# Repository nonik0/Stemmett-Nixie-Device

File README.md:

# Stemmett Nixie Device

## Description
A Nixie device that uses front-viewed [PL31 socket](https://tubes-store.com/product_info.php?products_id=101) Nixie tubes ([IN-4](https://www.tube-tester.com/sites/nixie/data/in-4/in-4-sh2.htm), [IN-7](https://www.tube-tester.com/sites/nixie/data/IN-7/in-7.htm), [IN-7A](https://www.swissnixie.com/tubes/IN7A/), IN-7B) in different orientations to create makeshift letters and spell things like names! The main board itself has 6 sockets for custom PL31 breakout boards, which have the nixie tube sockets in different orientations to rotate the Nixie tubes. By rotating the tubes we can pseudo-spell things, see images below for example (i.e. "7" rotated 180° to be an "L", or "m" rotated -90° to be a small-sized "E").

The hardware is designed in KiCad and all design files are included in the hardware directory. The hardware consists of the design of the main board PCB and three different versions of the PL31 socket breakout boards. The overall component choices target using simple through-hole components so the PCB is easier to debug, as it is my first PCB design. All cathodes of the nixie tubes are controlled with a single pin with serial, using three 74HC595 shift registers to control the input of the six old school К155ИД1 (K155ID1, SN74141) driver chips for each nixie tube. Each tube anode has a simple MOSFET circuit to be able to PWM each tube individually, allowing each tube to be individually dimmed or turned off. I am using the tiny awesome [NCH8200HV](https://www.tindie.com/products/omnixie/nch8200hv-nixie-high-voltage-power-module/) for the high voltage supply.

The firmware is a PlatformIO-based project targetting the [TinyS3](https://esp32s3.com/tinys3.html) ESP32 dev board. All source files are included in the firmware directory. The firmware will cycle through various different animations, returning to the configured name/word between each. It has a basic HTTP UX with REST interface to update settings--enable/disable animations, changing brightness, etc. It is simple to customize the firmware to any tube configuration by creating a new one in [board.h](firmware/board.h).

## Bowen Nixie Device
See the [Bowen Nixie Device README](hardware/kicad/bowen-nixie-device/README.md).

## Images

#### PCB Layout and Bare PCBs

#### Wood Block to Enclosure

#### Fitting and Finishing

#### Finished Enclosure

#### Alternate Enclosure

## Animations

<a href="images/glitch_anim.mp4">Glitch Animation</a>
<a href="images/random_scan_anim.mp4">Random Scan Animation</a>

TODO: animations in better lighting...

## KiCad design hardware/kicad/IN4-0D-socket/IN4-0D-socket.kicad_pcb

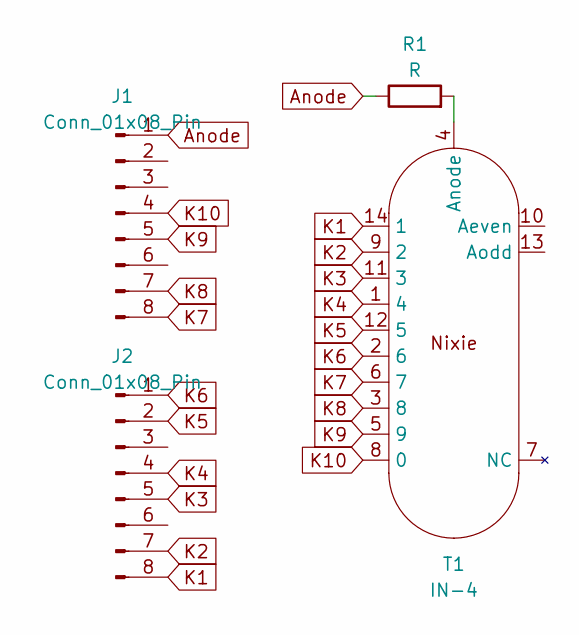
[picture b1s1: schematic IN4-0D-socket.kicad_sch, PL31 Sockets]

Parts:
J1, J2: Conn_01x08_Pin; PinHeader_1x08_P2.54mm_Vertical
R1: R; R_Axial_DIN0207_L6.3mm_D2.5mm_P7.62mm_Horizontal
T1: IN-4; PL31 (IN4 rotation)

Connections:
Anode: J1.1, R1.1
K1: J2.8, T1.14 (1)
K2: J2.7, T1.9 (2)
K3: J2.5, T1.11 (3)
K4: J2.4, T1.1 (4)
K5: J2.2, T1.12 (5)
K6: J2.1, T1.2 (6)
K7: J1.8, T1.6 (7)
K8: J1.7, T1.3 (8)
K9: J1.5, T1.5 (9)
K10: J1.4, T1.8 (0)
unnamed: R1.2, T1.4 (Anode)

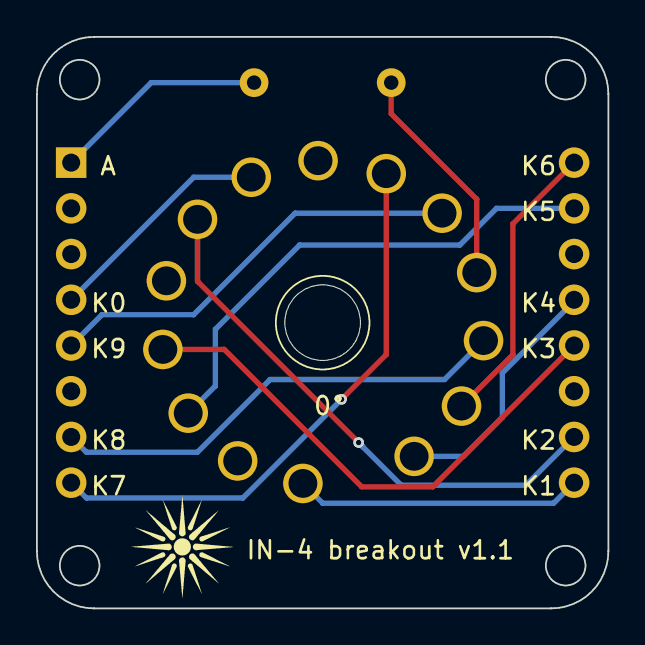
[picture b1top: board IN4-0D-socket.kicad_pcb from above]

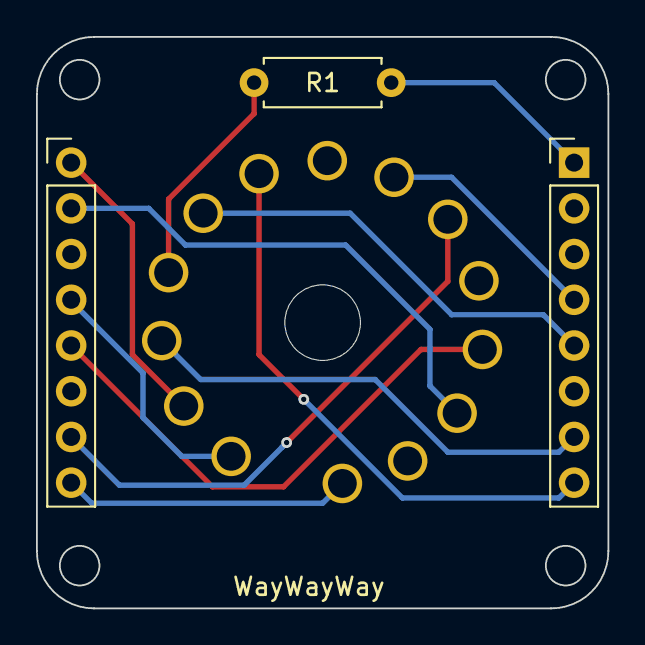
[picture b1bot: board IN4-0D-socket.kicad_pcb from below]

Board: 2 copper layers, 31.8 x 31.8 mm, 4 parts (3 on the bottom side), 12 nets.

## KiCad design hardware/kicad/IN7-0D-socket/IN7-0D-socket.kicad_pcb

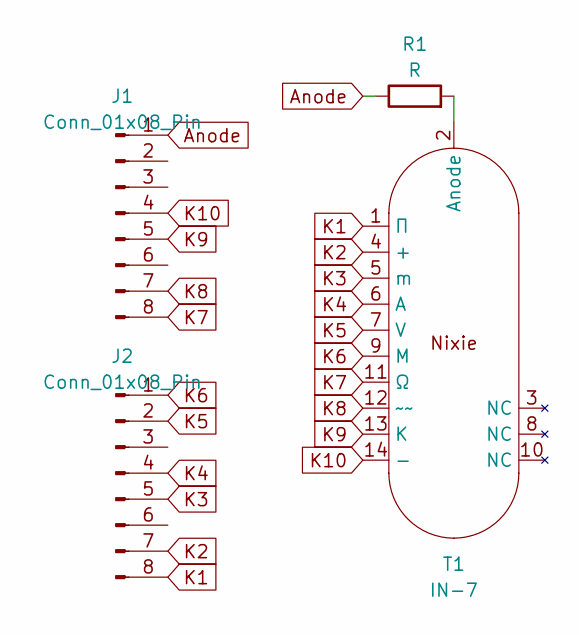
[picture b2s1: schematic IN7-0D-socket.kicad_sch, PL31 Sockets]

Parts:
J1, J2: Conn_01x08_Pin; PinHeader_1x08_P2.54mm_Vertical
R1: R; R_Axial_DIN0207_L6.3mm_D2.5mm_P7.62mm_Horizontal
T1: IN-7; PL31 (IN4 family)

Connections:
Anode: J1.1, R1.1
K1: J2.8, T1.1 (П)
K2: J2.7, T1.4 (+)
K3: J2.5, T1.5 (m)
K4: J2.4, T1.6 (A)
K5: J2.2, T1.7 (V)
K6: J2.1, T1.9 (M)
K7: J1.8, T1.11 (Ω)
K8: J1.7, T1.12 (~~)
K9: J1.5, T1.13 (К)
K10: J1.4, T1.14 (-)
unnamed: R1.2, T1.2 (Anode)

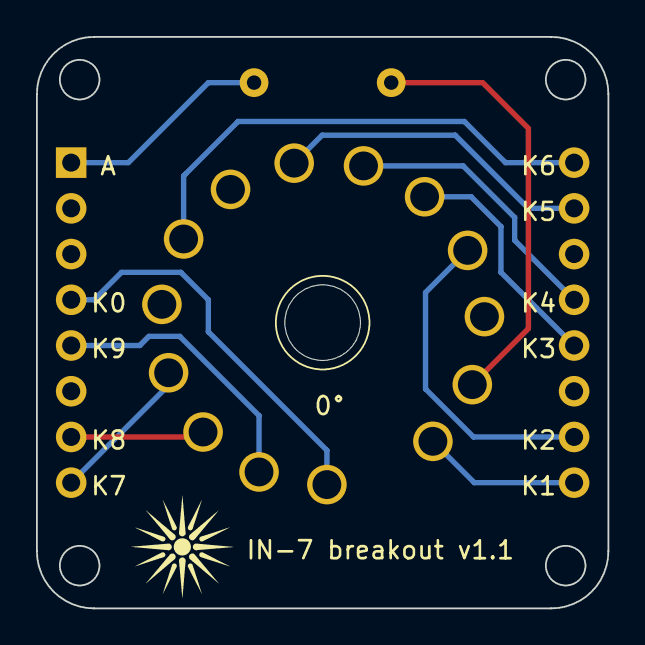
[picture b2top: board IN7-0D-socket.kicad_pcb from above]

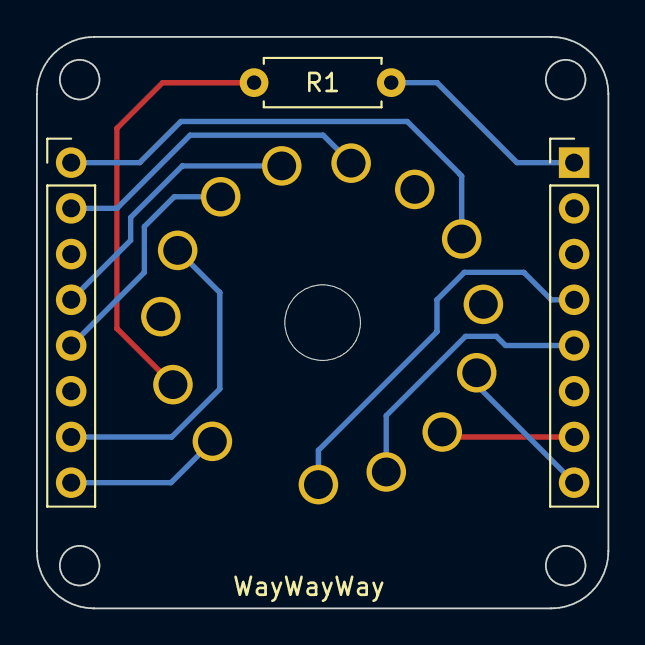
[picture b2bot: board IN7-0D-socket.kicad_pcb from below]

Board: 2 copper layers, 31.8 x 31.8 mm, 4 parts (3 on the bottom side), 12 nets.

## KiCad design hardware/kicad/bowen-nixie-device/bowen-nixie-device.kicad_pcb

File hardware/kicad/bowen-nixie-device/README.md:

# Bowen Nixie Device

## Description
A Nixie device that is a successor/companion to the original Stemmett Nixie Device. Like its predecessor, it uses front-viewed [PL31 socket](https://tubes-store.com/product_info.php?products_id=101) Nixie tubes ([IN-4](https://www.tube-tester.com/sites/nixie/data/in-4/in-4-sh2.htm), [IN-7](https://www.tube-tester.com/sites/nixie/data/IN-7/in-7.htm), [IN-7A](https://www.swissnixie.com/tubes/IN7A/), IN-7B) to spell words with makeshift letters. These Nixie tubes plug into custom PL31 breakout boards which orient the tubes in different rotations. Then these tube breakout boards plug into the main board that supports control of 4 tubes in total. More breakout board variations were added from the original project to enable more letter possible.

Bowen Nixie Device differs from the prior project primarily through some different component choices. In this version, I am primarily using SMD components and have included discrete cathode control for each tube, i.e. every cathode gets its own transistor for control. Cathode control remains the same as before, using a series of shift registers to control the gate for each transistor that controls the cathode on each tube. Each tube still has an anode control circuit for switching the high voltage on the tube's anode, allowing manual control of each tube's brightness with PWM. 

Hardware prototype is pending, firmware

## Work Left
- get new main board and tube breakout boards made
- create initial prototype, vet hardware design
- update existing firmware to work with new board and tube configuration

## Images

#### PCB Layout

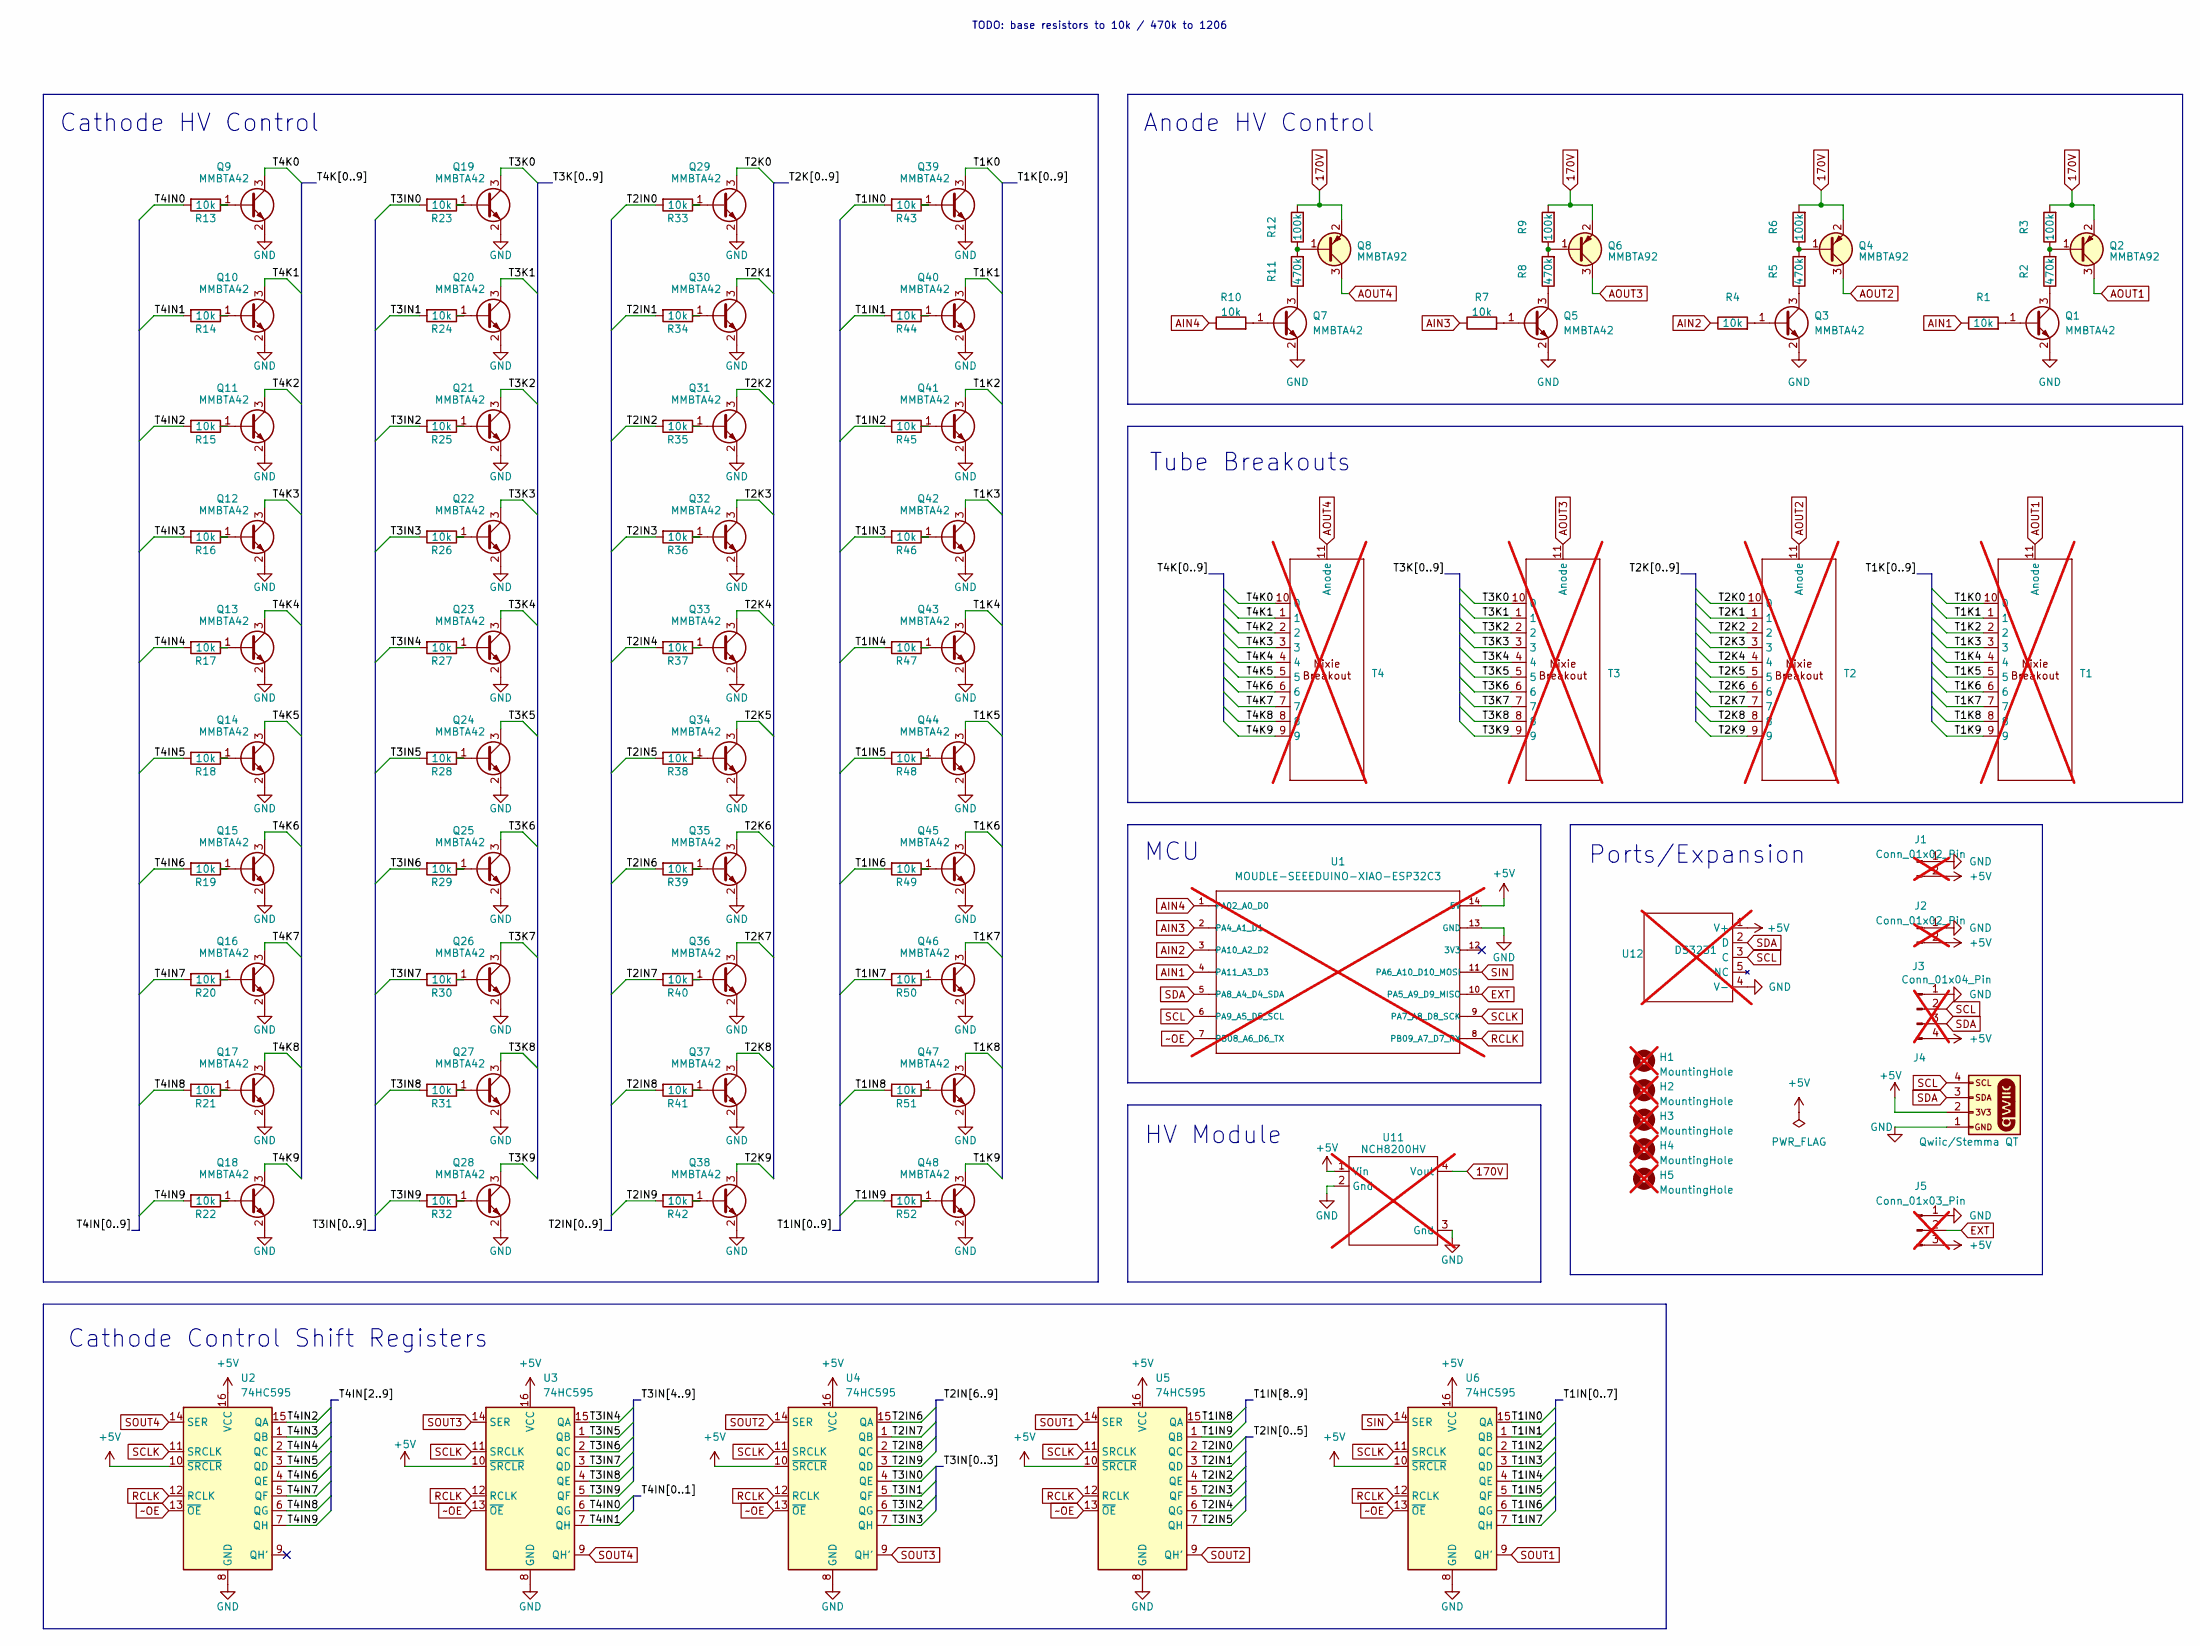
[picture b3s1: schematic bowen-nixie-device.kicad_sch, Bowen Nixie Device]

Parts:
H1, H2, H3, H4, H5: MountingHole; MountingHole_2.2mm_M2_DIN965_Pad; not fitted
J1, J2: Conn_01x02_Pin; PinSocket_1x02_P2.54mm_Vertical; not fitted
J3: Conn_01x04_Pin; PinSocket_1x04_P2.54mm_Vertical; not fitted
J4: Qwiic/Stemma QT; JST_1x04_P1.0mm_Vertical_SMD
J5: Conn_01x03_Pin; PinSocket_1x03_P2.54mm_Vertical; not fitted
Q1, Q3, Q5, Q7, Q9, Q10, Q11, Q12, Q13, Q14, Q15, Q16, Q17, Q18, Q19, Q20, Q21, Q22, Q23, Q24, Q25, Q26, Q27, Q28, Q29, Q30, Q31, Q32, Q33, Q34, Q35, Q36, Q37, Q38, Q39, Q40, Q41, Q42, Q43, Q44, Q45, Q46, Q47, Q48: MMBTA42; SOT-23
Q2, Q4, Q6, Q8: MMBTA92; SOT-23
R1, R4, R7, R10, R13, R14, R15, R16, R17, R18, R19, R20, R21, R22, R23, R24, R25, R26, R27, R28, R29, R30, R31, R32, R33, R34, R35, R36, R37, R38, R39, R40, R41, R42, R43, R44, R45, R46, R47, R48, R49, R50, R51, R52: 10k; R_0603_1608Metric
R2, R5, R8, R11: 470k; R_1206_3216Metric
R3, R6, R9, R12: 100k; R_0603_1608Metric
T1, T2, T3, T4: PL31 Socket Breakout; not fitted
U1: MOUDLE-SEEEDUINO-XIAO-ESP32C3; XIAO-ESP32-C3-DIP; not fitted
U2, U3, U4, U5, U6: 74HC595; SOIC-16_4.55x10.3mm_P1.27mm
U11: NCH8200HV; not fitted
U12: DS3231; DS3231 Breakout; not fitted

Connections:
170V: Q2.2 (E), Q4.2 (E), Q6.2 (E), Q8.2 (E), R3.2, R6.2, R9.2, R12.2, U11.4 (Vout)
+5V: J1.2, J2.2, J3.4, J4.2, J5.3, U1.14 (5V), U2.10 (~SRCLR), U2.16 (VCC), U3.10 (~SRCLR), U3.16 (VCC), U4.10 (~SRCLR), U4.16 (VCC), U5.10 (~SRCLR), U5.16 (VCC), U6.10 (~SRCLR), U6.16 (VCC), U11.1 (Vin), U12.1 (V+)
/T1IN0: R43.2, U6.15 (QA)
/T1IN1: R44.2, U6.1 (QB)
/T1IN2: R45.2, U6.2 (QC)
/T1IN3: R46.2, U6.3 (QD)
/T1IN4: R47.2, U6.4 (QE)
/T1IN5: R48.2, U6.5 (QF)
/T1IN6: R49.2, U6.6 (QG)
/T1IN7: R50.2, U6.7 (QH)
/T1IN8: R51.2, U5.15 (QA)
/T1IN9: R52.2, U5.1 (QB)
/T1K0: Q39.3 (C), T1.10 (0)
/T1K1: Q40.3 (C), T1.1
/T1K2: Q41.3 (C), T1.2
/T1K3: Q42.3 (C), T1.3
/T1K4: Q43.3 (C), T1.4
/T1K5: Q44.3 (C), T1.5
/T1K6: Q45.3 (C), T1.6
/T1K7: Q46.3 (C), T1.7
/T1K8: Q47.3 (C), T1.8
/T1K9: Q48.3 (C), T1.9
/T2IN0: R33.2, U5.2 (QC)
/T2IN1: R34.2, U5.3 (QD)
/T2IN2: R35.2, U5.4 (QE)
/T2IN3: R36.2, U5.5 (QF)
/T2IN4: R37.2, U5.6 (QG)
/T2IN5: R38.2, U5.7 (QH)
/T2IN6: R39.2, U4.15 (QA)
/T2IN7: R40.2, U4.1 (QB)
/T2IN8: R41.2, U4.2 (QC)
/T2IN9: R42.2, U4.3 (QD)
/T2K0: Q29.3 (C), T2.10 (0)
/T2K1: Q30.3 (C), T2.1
/T2K2: Q31.3 (C), T2.2
/T2K3: Q32.3 (C), T2.3
/T2K4: Q33.3 (C), T2.4
/T2K5: Q34.3 (C), T2.5
/T2K6: Q35.3 (C), T2.6
/T2K7: Q36.3 (C), T2.7
/T2K8: Q37.3 (C), T2.8
/T2K9: Q38.3 (C), T2.9
/T3IN0: R23.2, U4.4 (QE)
/T3IN1: R24.2, U4.5 (QF)
/T3IN2: R25.2, U4.6 (QG)
/T3IN3: R26.2, U4.7 (QH)
/T3IN4: R27.2, U3.15 (QA)
/T3IN5: R28.2, U3.1 (QB)
/T3IN6: R29.2, U3.2 (QC)
/T3IN7: R30.2, U3.3 (QD)
/T3IN8: R31.2, U3.4 (QE)
/T3IN9: R32.2, U3.5 (QF)
/T3K0: Q19.3 (C), T3.10 (0)
/T3K1: Q20.3 (C), T3.1
/T3K2: Q21.3 (C), T3.2
/T3K3: Q22.3 (C), T3.3
/T3K4: Q23.3 (C), T3.4
/T3K5: Q24.3 (C), T3.5
/T3K6: Q25.3 (C), T3.6
/T3K7: Q26.3 (C), T3.7
/T3K8: Q27.3 (C), T3.8
/T3K9: Q28.3 (C), T3.9
/T4IN0: R13.2, U3.6 (QG)
/T4IN1: R14.2, U3.7 (QH)
/T4IN2: R15.2, U2.15 (QA)
/T4IN3: R16.2, U2.1 (QB)
/T4IN4: R17.2, U2.2 (QC)
/T4IN5: R18.2, U2.3 (QD)
/T4IN6: R19.2, U2.4 (QE)
/T4IN7: R20.2, U2.5 (QF)
/T4IN8: R21.2, U2.6 (QG)
/T4IN9: R22.2, U2.7 (QH)
/T4K0: Q9.3 (C), T4.10 (0)
/T4K1: Q10.3 (C), T4.1
/T4K2: Q11.3 (C), T4.2
/T4K3: Q12.3 (C), T4.3
/T4K4: Q13.3 (C), T4.4
/T4K5: Q14.3 (C), T4.5
/T4K6: Q15.3 (C), T4.6
/T4K7: Q16.3 (C), T4.7
/T4K8: Q17.3 (C), T4.8
/T4K9: Q18.3 (C), T4.9
AIN1: R1.1, U1.4 (PA11_A3_D3)
AIN2: R4.1, U1.3 (PA10_A2_D2)
AIN3: R7.1, U1.2 (PA4_A1_D1)
AIN4: R10.1, U1.1 (PA02_A0_D0)
AOUT1: Q2.3 (C), T1.11 (Anode)
AOUT2: Q4.3 (C), T2.11 (Anode)
AOUT3: Q6.3 (C), T3.11 (Anode)
AOUT4: Q8.3 (C), T4.11 (Anode)
EXT: J5.2, U1.10 (PA5_A9_D9_MISO)
GND: J1.1, J2.1, J3.1, J4.1, J5.1, Q1.2 (E), Q3.2 (E), Q5.2 (E), Q7.2 (E), Q9.2 (E), Q10.2 (E), Q11.2 (E), Q12.2 (E), Q13.2 (E), Q14.2 (E), Q15.2 (E), Q16.2 (E), Q17.2 (E), Q18.2 (E), Q19.2 (E), Q20.2 (E), Q21.2 (E), Q22.2 (E), Q23.2 (E), Q24.2 (E), Q25.2 (E), Q26.2 (E), Q27.2 (E), Q28.2 (E), Q29.2 (E), Q30.2 (E), Q31.2 (E), Q32.2 (E), Q33.2 (E), Q34.2 (E), Q35.2 (E), Q36.2 (E), Q37.2 (E), Q38.2 (E), Q39.2 (E), Q40.2 (E), Q41.2 (E), Q42.2 (E), Q43.2 (E), Q44.2 (E), Q45.2 (E), Q46.2 (E), Q47.2 (E), Q48.2 (E), U1.13 (GND), U2.8 (GND), U3.8 (GND), U4.8 (GND), U5.8 (GND), U6.8 (GND), U11.2 (Gnd), U11.3 (Gnd), U12.4 (V-)
unnamed: Q1.1 (B), R1.2
unnamed: Q1.3 (C), R2.1
unnamed: Q2.1 (B), R2.2, R3.1
unnamed: Q3.1 (B), R4.2
unnamed: Q3.3 (C), R5.1
unnamed: Q4.1 (B), R5.2, R6.1
unnamed: Q5.1 (B), R7.2
unnamed: Q5.3 (C), R8.1
unnamed: Q6.1 (B), R8.2, R9.1
unnamed: Q7.1 (B), R10.2
unnamed: Q7.3 (C), R11.1
unnamed: Q8.1 (B), R11.2, R12.1
unnamed: Q9.1 (B), R13.1
unnamed: Q10.1 (B), R14.1
unnamed: Q11.1 (B), R15.1
unnamed: Q12.1 (B), R16.1
unnamed: Q13.1 (B), R17.1
unnamed: Q14.1 (B), R18.1
unnamed: Q15.1 (B), R19.1
unnamed: Q16.1 (B), R20.1
unnamed: Q17.1 (B), R21.1
unnamed: Q18.1 (B), R22.1
unnamed: Q19.1 (B), R23.1
unnamed: Q20.1 (B), R24.1
unnamed: Q21.1 (B), R25.1
unnamed: Q22.1 (B), R26.1
unnamed: Q23.1 (B), R27.1
unnamed: Q24.1 (B), R28.1
unnamed: Q25.1 (B), R29.1
unnamed: Q26.1 (B), R30.1
unnamed: Q27.1 (B), R31.1
unnamed: Q28.1 (B), R32.1
unnamed: Q29.1 (B), R33.1
unnamed: Q30.1 (B), R34.1
unnamed: Q31.1 (B), R35.1
unnamed: Q32.1 (B), R36.1
unnamed: Q33.1 (B), R37.1
unnamed: Q34.1 (B), R38.1
unnamed: Q35.1 (B), R39.1
unnamed: Q36.1 (B), R40.1
unnamed: Q37.1 (B), R41.1
unnamed: Q38.1 (B), R42.1
unnamed: Q39.1 (B), R43.1
unnamed: Q40.1 (B), R44.1
unnamed: Q41.1 (B), R45.1
unnamed: Q42.1 (B), R46.1
unnamed: Q43.1 (B), R47.1
unnamed: Q44.1 (B), R48.1
unnamed: Q45.1 (B), R49.1
unnamed: Q46.1 (B), R50.1
unnamed: Q47.1 (B), R51.1
unnamed: Q48.1 (B), R52.1
RCLK: U1.8 (PB09_A7_D7_RX), U2.12 (RCLK), U3.12 (RCLK), U4.12 (RCLK), U5.12 (RCLK), U6.12 (RCLK)
SCL: J3.2, J4.4, U1.6 (PA9_A5_D5_SCL), U12.3 (C)
SCLK: U1.9 (PA7_A8_D8_SCK), U2.11 (SRCLK), U3.11 (SRCLK), U4.11 (SRCLK), U5.11 (SRCLK), U6.11 (SRCLK)
SDA: J3.3, J4.3, U1.5 (PA8_A4_D4_SDA), U12.2 (D)
SIN: U1.11 (PA6_A10_D10_MOSI), U6.14 (SER)
SOUT1: U5.14 (SER), U6.9 (QH')
SOUT2: U4.14 (SER), U5.9 (QH')
SOUT3: U3.14 (SER), U4.9 (QH')
SOUT4: U2.14 (SER), U3.9 (QH')
~OE: U1.7 (PB08_A6_D6_TX), U2.13 (~OE), U3.13 (~OE), U4.13 (~OE), U5.13 (~OE), U6.13 (~OE)

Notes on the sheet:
TODO: base resistors to 10k / 470k to 1206
Cathode Control Shift Registers
Cathode HV Control
HV Module
Anode HV Control
Tube Breakouts
Ports/Expansion
MCU

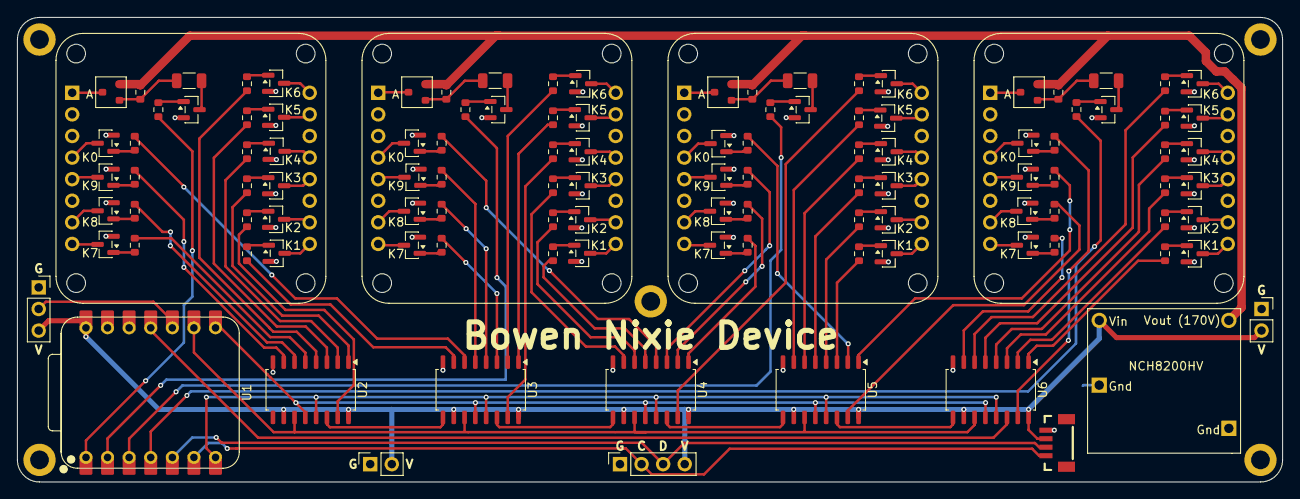
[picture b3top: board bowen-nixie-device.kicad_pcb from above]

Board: 2 copper layers, 148.8 x 54.6 mm, 121 parts (0 on the bottom side), 154 nets.

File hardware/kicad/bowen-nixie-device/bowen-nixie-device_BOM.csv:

"Reference","Qty","Value","Footprint","Description","MPN","Package"
"J4","1","Qwiic/Stemma QT","PCM_SparkFun-Connector:JST_1x04_P1.0mm_Vertical_SMD","4 pin JST 1mm polarized connector for I2C","BM04B-SRSS-TB",""
"Q2,Q4,Q6,Q8","4","MMBTA92","Package_TO_SOT_SMD:SOT-23","0.5A Ic, 300V Vce, PNP High Voltage Transistor, SOT-23","MMBTA92LT1G","SOT-23"
"Q1,Q3,Q5,Q7,Q9,Q10,Q11,Q12,Q13,Q14,Q15,Q16,Q17,Q18,Q19,Q20,Q21,Q22,Q23,Q24,Q25,Q26,Q27,Q28,Q29,Q30,Q31,Q32,Q33,Q34,Q35,Q36,Q37,Q38,Q39,Q40,Q41,Q42,Q43,Q44,Q45,Q46,Q47,Q48","44","MMBTA42","Package_TO_SOT_SMD:SOT-23","0.5A Ic, 300V Vce, NPN High Voltage Transistor, SOT-23","MMBTA42LT1G","SOT-23"
"U2,U3,U4,U5,U6","5","74HC595","Package_SO:SOIC-16_4.55x10.3mm_P1.27mm","8-bit serial in/out Shift Register 3-State Outputs","74HC595D","SOIC-16"
"R2,R5,R8,R11","4","470k","Resistor_SMD:R_1206_3216Metric","R 0603 470K","RC1206FR-07470KL","1206"
"R3,R6,R9,R12","4","100k","Resistor_SMD:R_0603_1608Metric","R 0603 100k","RC0402FR-07100KL","0603"
"R1,R4,R7,R10,R13,R14,R15,R16,R17,R18,R19,R20,R21,R22,R23,R24,R25,R26,R27,R28,R29,R30,R31,R32,R33,R34,R35,R36,R37,R38,R39,R40,R41,R42,R43,R44,R45,R46,R47,R48,R49,R50,R51,R52","44","10k","Resistor_SMD:R_0603_1608Metric","R 0603 10k","RC0603JR-0710KL","0603"

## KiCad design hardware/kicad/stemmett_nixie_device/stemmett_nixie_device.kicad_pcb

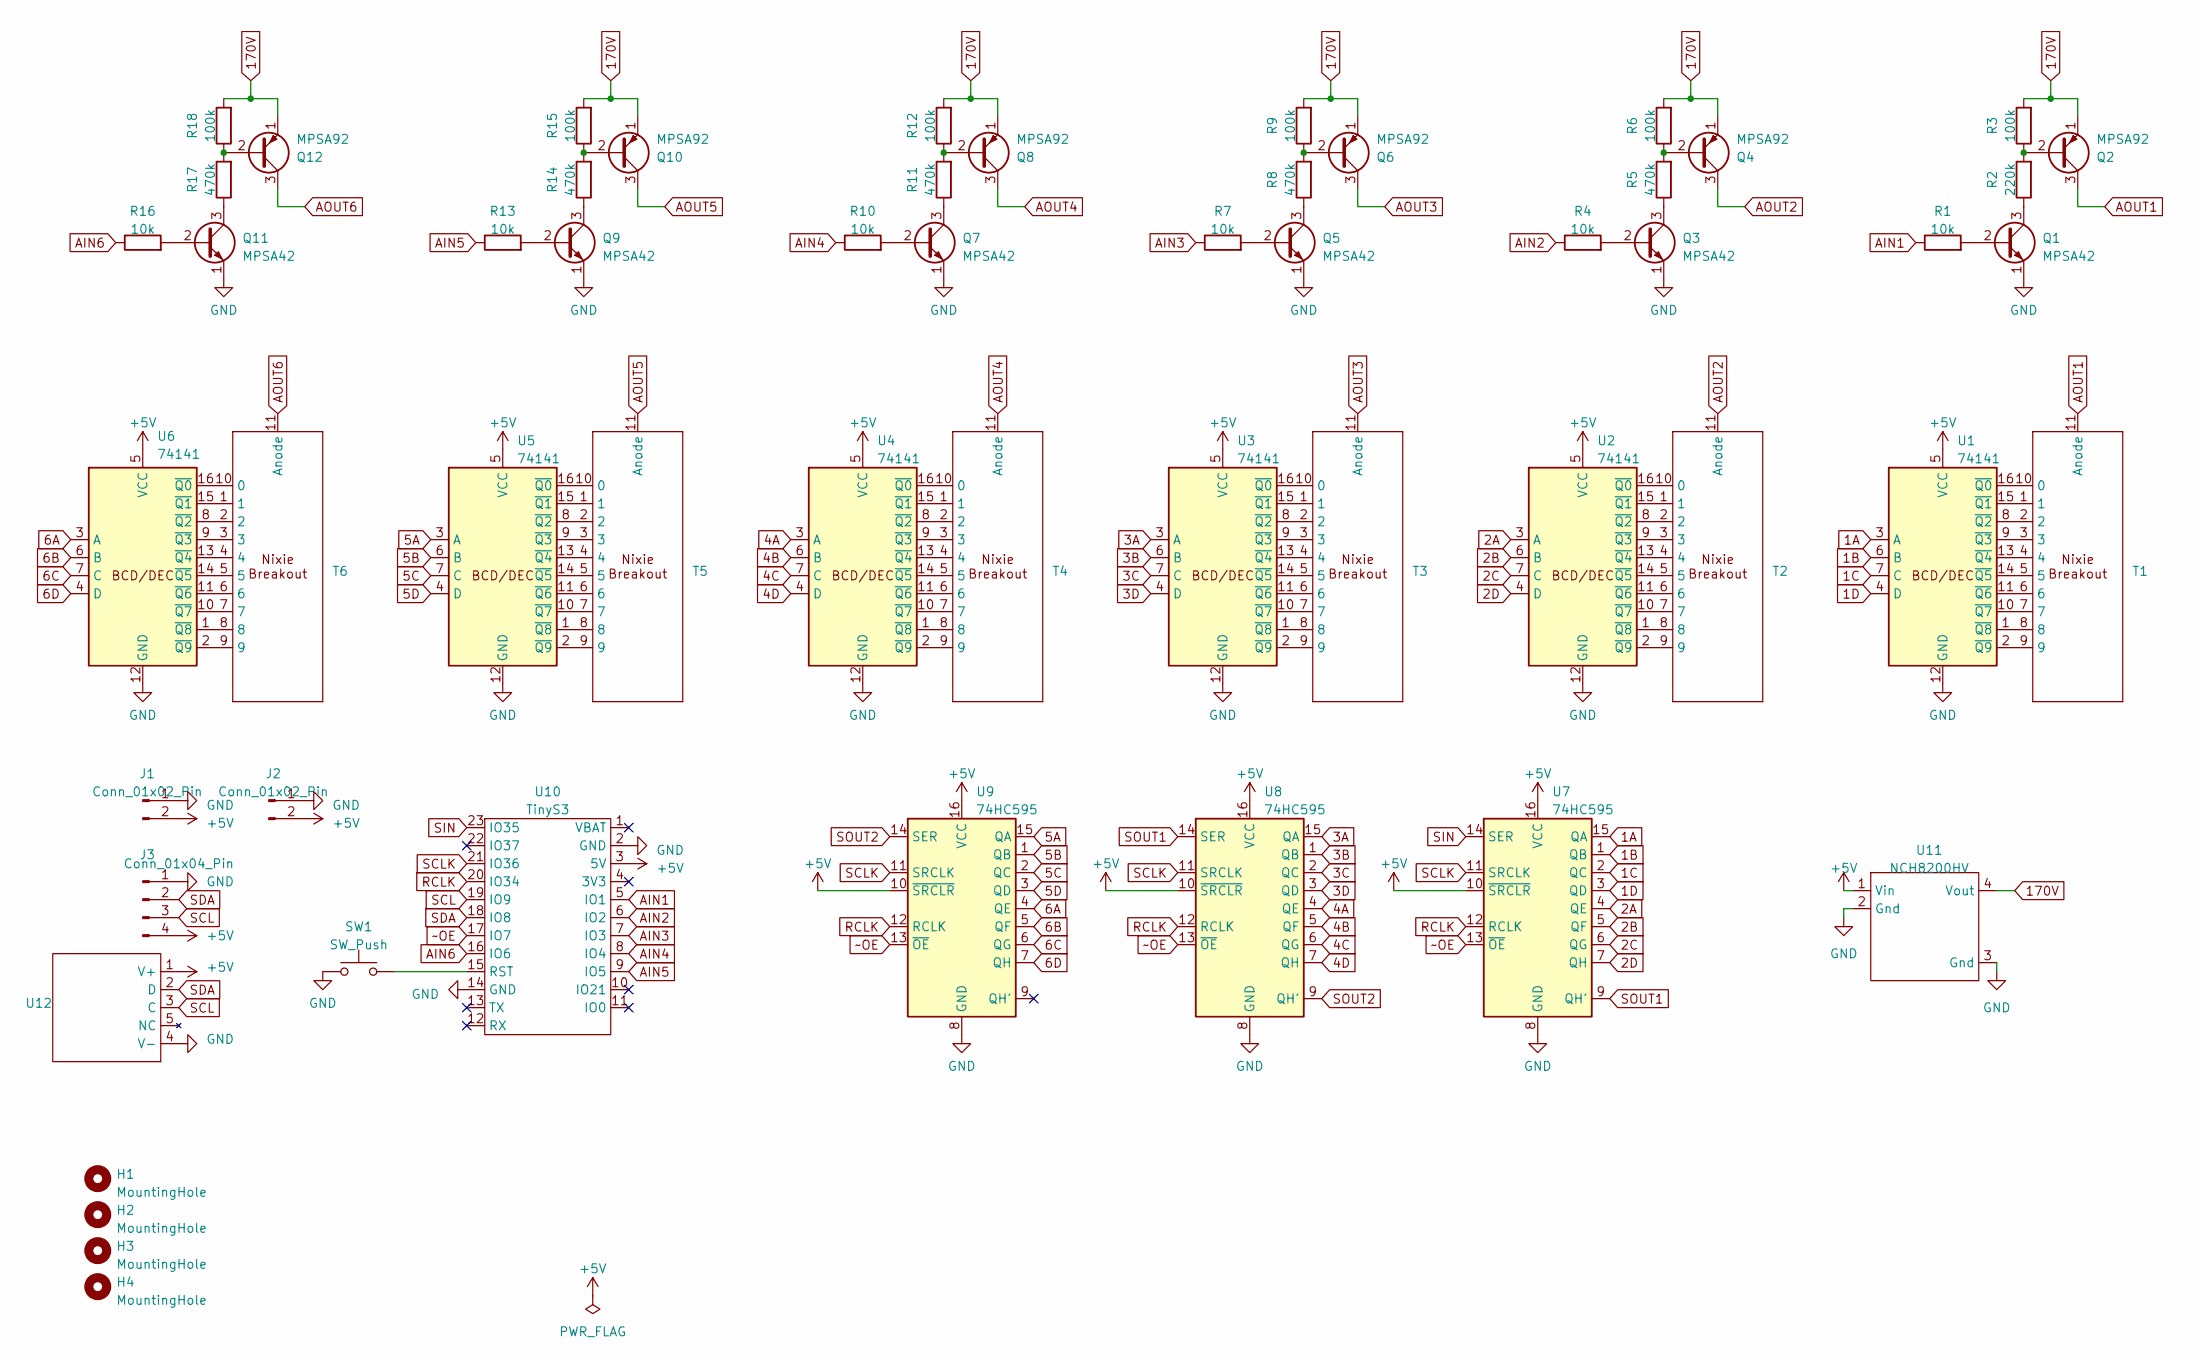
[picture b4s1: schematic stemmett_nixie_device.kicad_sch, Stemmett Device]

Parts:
H1, H2, H3, H4: MountingHole; MountingHole_2.2mm_M2
J1, J2: Conn_01x02_Pin; PinSocket_1x02_P2.54mm_Vertical
J3: Conn_01x04_Pin; PinSocket_1x04_P2.54mm_Vertical
Q1, Q3, Q5, Q7, Q9, Q11: MPSA42; TO-92_Inline
Q2, Q4, Q6, Q8, Q10, Q12: MPSA92; TO-92_Inline
R1, R4, R7, R10, R13, R16: 10k; R_Axial_DIN0207_L6.3mm_D2.5mm_P7.62mm_Horizontal
R2: 220k; R_Axial_DIN0207_L6.3mm_D2.5mm_P7.62mm_Horizontal
R3, R6, R9, R12, R15, R18: 100k; R_Axial_DIN0207_L6.3mm_D2.5mm_P7.62mm_Horizontal
R5, R8, R11, R14, R17: 470k; R_Axial_DIN0207_L6.3mm_D2.5mm_P7.62mm_Horizontal
SW1: SW_Push; SW_PUSH_6mm
T1, T2, T3, T4, T5, T6: PL31 Socket Breakout
U1, U2, U3, U4, U5, U6: 74141; DIP-16_W7.62mm
U7, U8, U9: 74HC595; DIP-16_W7.62mm
U10: TinyS3
U11: NCH8200HV
U12: DS3231 Breakout

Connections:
1A: U1.3 (A), U7.15 (QA)
1B: U1.6 (B), U7.1 (QB)
1C: U1.7 (C), U7.2 (QC)
1D: U1.4 (D), U7.3 (QD)
2A: U2.3 (A), U7.4 (QE)
2B: U2.6 (B), U7.5 (QF)
2C: U2.7 (C), U7.6 (QG)
2D: U2.4 (D), U7.7 (QH)
3A: U3.3 (A), U8.15 (QA)
3B: U3.6 (B), U8.1 (QB)
3C: U3.7 (C), U8.2 (QC)
3D: U3.4 (D), U8.3 (QD)
4A: U4.3 (A), U8.4 (QE)
4B: U4.6 (B), U8.5 (QF)
4C: U4.7 (C), U8.6 (QG)
4D: U4.4 (D), U8.7 (QH)
5A: U5.3 (A), U9.15 (QA)
5B: U5.6 (B), U9.1 (QB)
5C: U5.7 (C), U9.2 (QC)
5D: U5.4 (D), U9.3 (QD)
6A: U6.3 (A), U9.4 (QE)
6B: U6.6 (B), U9.5 (QF)
6C: U6.7 (C), U9.6 (QG)
6D: U6.4 (D), U9.7 (QH)
170V: Q2.1 (E), Q4.1 (E), Q6.1 (E), Q8.1 (E), Q10.1 (E), Q12.1 (E), R3.2, R6.2, R9.2, R12.2, R15.2, R18.2, U11.4 (Vout)
+5V: J1.2, J2.2, J3.4, U1.5 (VCC), U2.5 (VCC), U3.5 (VCC), U4.5 (VCC), U5.5 (VCC), U6.5 (VCC), U7.10 (~SRCLR), U7.16 (VCC), U8.10 (~SRCLR), U8.16 (VCC), U9.10 (~SRCLR), U9.16 (VCC), U10.3 (5V), U11.1 (Vin), U12.1 (V+)
AIN1: R1.1, U10.5 (IO1)
AIN2: R4.1, U10.6 (IO2)
AIN3: R7.1, U10.7 (IO3)
AIN4: R10.1, U10.8 (IO4)
AIN5: R13.1, U10.9 (IO5)
AIN6: R16.1, U10.16 (IO6)
AOUT1: Q2.3 (C), T1.11 (Anode)
AOUT2: Q4.3 (C), T2.11 (Anode)
AOUT3: Q6.3 (C), T3.11 (Anode)
AOUT4: Q8.3 (C), T4.11 (Anode)
AOUT5: Q10.3 (C), T5.11 (Anode)
AOUT6: Q12.3 (C), T6.11 (Anode)
GND: J1.1, J2.1, J3.1, Q1.1 (E), Q3.1 (E), Q5.1 (E), Q7.1 (E), Q9.1 (E), Q11.1 (E), SW1.1, U1.12 (GND), U2.12 (GND), U3.12 (GND), U4.12 (GND), U5.12 (GND), U6.12 (GND), U7.8 (GND), U8.8 (GND), U9.8 (GND), U10.2 (GND), U10.14 (GND), U11.2 (Gnd), U11.3 (Gnd), U12.4 (V-)
unnamed: Q1.2 (B), R1.2
unnamed: Q1.3 (C), R2.1
unnamed: Q2.2 (B), R2.2, R3.1
unnamed: Q3.2 (B), R4.2
unnamed: Q3.3 (C), R5.1
unnamed: Q4.2 (B), R5.2, R6.1
unnamed: Q5.2 (B), R7.2
unnamed: Q5.3 (C), R8.1
unnamed: Q6.2 (B), R8.2, R9.1
unnamed: Q7.2 (B), R10.2
unnamed: Q7.3 (C), R11.1
unnamed: Q8.2 (B), R11.2, R12.1
unnamed: Q9.2 (B), R13.2
unnamed: Q9.3 (C), R14.1
unnamed: Q10.2 (B), R14.2, R15.1
unnamed: Q11.2 (B), R16.2
unnamed: Q11.3 (C), R17.1
unnamed: Q12.2 (B), R17.2, R18.1
unnamed: T1.10 (0), U1.16 (~Q0)
unnamed: T2.10 (0), U2.16 (~Q0)
unnamed: T3.10 (0), U3.16 (~Q0)
unnamed: T4.10 (0), U4.16 (~Q0)
unnamed: T5.10 (0), U5.16 (~Q0)
unnamed: T6.10 (0), U6.16 (~Q0)
unnamed: T1.1, U1.15 (~Q1)
unnamed: T1.2, U1.8 (~Q2)
unnamed: T1.3, U1.9 (~Q3)
unnamed: T1.4, U1.13 (~Q4)
unnamed: T1.5, U1.14 (~Q5)
unnamed: T1.6, U1.11 (~Q6)
unnamed: T1.7, U1.10 (~Q7)
unnamed: T1.8, U1.1 (~Q8)
unnamed: T1.9, U1.2 (~Q9)
unnamed: T2.1, U2.15 (~Q1)
unnamed: T2.2, U2.8 (~Q2)
unnamed: T2.3, U2.9 (~Q3)
unnamed: T2.4, U2.13 (~Q4)
unnamed: T2.5, U2.14 (~Q5)
unnamed: T2.6, U2.11 (~Q6)
unnamed: T2.7, U2.10 (~Q7)
unnamed: T2.8, U2.1 (~Q8)
unnamed: T2.9, U2.2 (~Q9)
unnamed: T3.1, U3.15 (~Q1)
unnamed: T3.2, U3.8 (~Q2)
unnamed: T3.3, U3.9 (~Q3)
unnamed: T3.4, U3.13 (~Q4)
unnamed: T3.5, U3.14 (~Q5)
unnamed: T3.6, U3.11 (~Q6)
unnamed: T3.7, U3.10 (~Q7)
unnamed: T3.8, U3.1 (~Q8)
unnamed: T3.9, U3.2 (~Q9)
unnamed: T4.1, U4.15 (~Q1)
unnamed: T4.2, U4.8 (~Q2)
unnamed: T4.3, U4.9 (~Q3)
unnamed: T4.4, U4.13 (~Q4)
unnamed: T4.5, U4.14 (~Q5)
unnamed: T4.6, U4.11 (~Q6)
unnamed: T4.7, U4.10 (~Q7)
unnamed: T4.8, U4.1 (~Q8)
unnamed: T4.9, U4.2 (~Q9)
unnamed: T5.1, U5.15 (~Q1)
unnamed: T5.2, U5.8 (~Q2)
unnamed: T5.3, U5.9 (~Q3)
unnamed: T5.4, U5.13 (~Q4)
unnamed: T5.5, U5.14 (~Q5)
unnamed: T5.6, U5.11 (~Q6)
unnamed: T5.7, U5.10 (~Q7)
unnamed: T5.8, U5.1 (~Q8)
unnamed: T5.9, U5.2 (~Q9)
unnamed: T6.1, U6.15 (~Q1)
unnamed: T6.2, U6.8 (~Q2)
unnamed: T6.3, U6.9 (~Q3)
unnamed: T6.4, U6.13 (~Q4)
unnamed: T6.5, U6.14 (~Q5)
unnamed: T6.6, U6.11 (~Q6)
unnamed: T6.7, U6.10 (~Q7)
unnamed: T6.8, U6.1 (~Q8)
unnamed: T6.9, U6.2 (~Q9)
unnamed: SW1.2, U10.15 (RST)
RCLK: U7.12 (RCLK), U8.12 (RCLK), U9.12 (RCLK), U10.20 (IO34)
SCL: J3.3, U10.19 (IO9), U12.3 (C)
SCLK: U7.11 (SRCLK), U8.11 (SRCLK), U9.11 (SRCLK), U10.21 (IO36)
SDA: J3.2, U10.18 (IO8), U12.2 (D)
SIN: U7.14 (SER), U10.23 (IO35)
SOUT1: U7.9 (QH'), U8.14 (SER)
SOUT2: U8.9 (QH'), U9.14 (SER)
~OE: U7.13 (~OE), U8.13 (~OE), U9.13 (~OE), U10.17 (IO7)

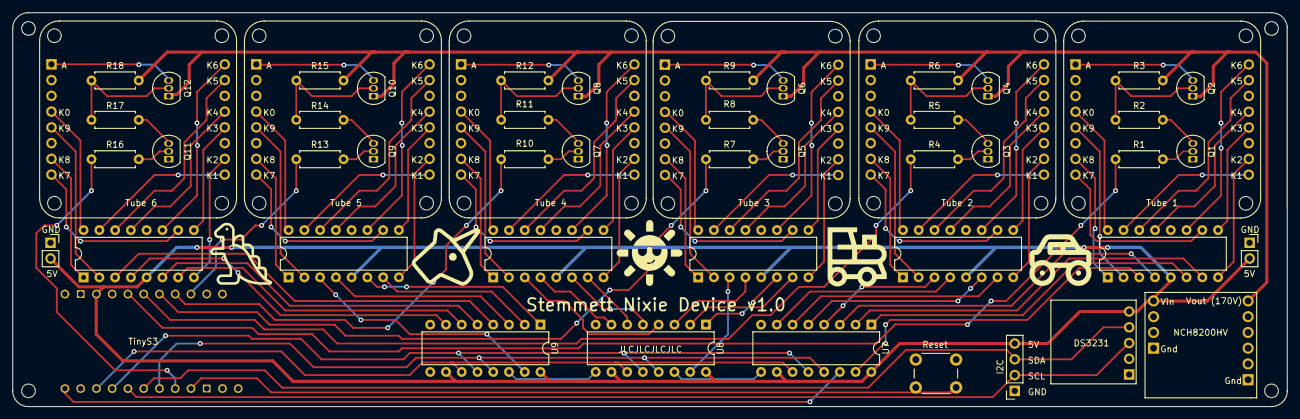
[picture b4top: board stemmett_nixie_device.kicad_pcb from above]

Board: 2 copper layers, 205.5 x 63.5 mm, 56 parts (0 on the bottom side), 126 nets.

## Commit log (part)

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2023-04-10 basic PWM animation
2023-04-11 starting work for animations
2023-04-11 animation updates
2023-04-16 new animations, code organization
2023-04-27 fade animation initial work, not working
2023-04-30 fade animation work
2023-05-02 fade fit and finish
2023-05-02 misc updates
2023-05-03 RTC stuff
2023-05-06 slotmachineanimation updates
2023-05-11 bubble fade initial impl
2023-05-11 partial fix
2023-05-12 bubble fade working
2023-05-12 slotHelper refactor
2023-05-13 slot helper fixes
2023-05-13 cylon partial updates
2023-05-14 cylon and slot helper refactoring
2023-05-14 cylon fit and finish and refactoring
2023-05-16 start for pulsar, other updates
2023-05-19 pulsar animation starting work
2023-05-19 more pulsar work
2023-05-22 slot helper refactor, other updates
2023-05-22 fixes from refactoring
2023-05-22 pulsar mostly done
2023-05-27 minor updates
2023-06-26 new rain animation
2023-06-27 renaming animations and fixes
2023-06-27 slot helper update+
2023-06-29 new scan animation
2023-06-29 emmett updates
2023-08-01 start for rest api
2024-01-26 adding kicad files
2024-01-26 delete
2024-01-26 git cleanup
2024-03-14 rest api work
2024-03-16 rest api, refactoring
2024-03-23 changing dir structure
2024-03-23 rest looking good
2024-03-23 settings, more rest
2024-03-23 rest and rtc updates
2024-03-24 index cleanup, mDNS
2024-03-24 readme
2024-07-05 day/night animation control and bug fixes for brightness transitioning
2024-07-22 initial work for animation speed control
2024-09-18 lots of animation speed adjustments
2024-10-28 wifi changes temp?
2024-12-09 fixes
2024-12-11 various updates/refactor, tasks, light sensor
2024-12-12 control for light threshold, fixes
2024-12-12 minor
2025-10-02 old adjustments
2025-10-02 pwm fixes
2025-10-06 ghost anim refactor
2025-10-06 bubble animation refactor
2025-10-06 rain animation refactor
2025-10-08 wifi man flag
2025-10-16 3DP design files for two different cases/enclosures
2025-10-25 minimal display control
2025-10-29 rest changes
2025-10-29 tube test boot anim
2025-10-30 custom tube config
2025-11-06 initial start for Bowen Nixie Device, rough schematic
2025-11-07 adding photos of finished projects
2025-11-25 bowen schematic progress
2026-01-15 schematic passing ERC
2026-01-15 rough initial layout
2026-03-18 bowen progress
2026-04-09 bowen layout progress
2026-04-09 pcb tracing progress
2026-04-09 more trace adjs
2026-04-13 trace progress, gnd plane and most traces
2026-04-13 layout final
2026-04-14 bowen passing drc layout
2026-04-15 IN-4 0D socket
2026-04-15 IN-7 180D socket
2026-04-15 IN-7 90D socket
2026-04-17 bowen updates
